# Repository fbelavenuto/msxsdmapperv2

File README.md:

# MSX SD Mapper V2

## WARNING: do not try to update the old SDMapper V1 (and its clones) with this new ROM using the old SDMUPD.COM utility, as the hardware is different, and it will brick your cartridge.

# Disclaimer

This documentation describes Open Hardware and is licensed under the CERN OHL v. 1.1.

You may redistribute and modify this documentation under the terms of the [CERN OHL v.1.1](http://ohwr.org/cernohl). This documentation is distributed WITHOUT ANY EXPRESS OR IMPLIED WARRANTY, INCLUDING OF MERCHANTABILITY, SATISFACTORY QUALITY AND FITNESS FOR A PARTICULAR PURPOSE.

Please see the CERN OHL v.1.1 for applicable conditions

# Project description

This project implements a cartridge-shaped interface to add a mass storage device using up to two SD (Secure Digital) and a 512K Mapper for MSX line computers.

[Nextor](http://www.konamiman.com/msx/msx-e.html#nextor) was used as operating system, being developed only the driver to have access to the two SD cards. Nextor is an open project.

Nextor is an evolution of MSX-DOS 2 natively supporting FAT16 partitions up to 4GB, and can have 4 partitions per SD card. 128KB of Mapper is required on the minimum to use Nextor with access to sub-directories, less than 128K mapper only allows the use of the MSXDOS1 kernel, limiting partitions with FAT12 and maximum 16MB per partition.

One of the switches enables or disables the Mapper in conjunction with a slot expander. The second key allows you to select between two driver options, useful for having a backup a stable version of the driver and use it to restore a new driver update failed.

A utility called "FBL-UPD.COM" was created to be able to update the flash by MSX itself.

To compile the FBL-UPD.COM driver and utility use the [Konaniman's Nestor80](https://github.com/Konamiman/Nestor80) and to compile the CPLD code use [Xilinx ISE Webpack](https://www.xilinx.com/support/download/index.html/content/xilinx/en/downloadNav/vivado-design-tools/archive-ise.html).

Technical details:
 - The CPLD code implements all the necessary logic, implementing an expander of standard slots, one SPI mode 0 port, standard ASCII16 MegaROM control used by Nextor and the 512K Mapper control.
 - When activating the mapper, the interface activates the slot expander, and with that the interface works only on non-expanded slots. However, if you disable the mapper, the slot expander is disabled, allowing you to use the device of mass storage in expanded slots. the mass storage device is in subslot 0 and the mapper device in subslot 1.
 - There is a window in $7B00~7EFF for SPI data transfer.
 - There is a configuration and status register at address $7FF0 and a small timer at address $7FF1. More details in the driver source.

# Acknowledge

Thanks to FRS for rewriting the driver, to Luciano Sturaro for board routing and the MSXBR-L community for their support and encouragement.

# Quickstart guide

After assembling the device, or buying a ready-made one, get an SD card, put it in the interface and start MSX.

When dropping into BASIC, type `CALL FDISK` to start formatting the SD card. The FAT16 file system used by Nextor supports a maximum of 4GB.

After partitioning and formatting, shut down MSX, remove the SD card and put it on your PC, copy the contents of the ./SD folder into the first partition of the SD card and put it back in MSX.

For more information on how to use Nextor, visit [User Manual](https://github.com/Konamiman/Nextor/blob/v2.1/docs/Nextor%202.1%20User%20Manual.md)

# 3D case

I found [this design](https://www.printables.com/en/model/496236-msx-cartridge-for-fblabs-sd-mapper-v2) made by community.

# Readme in portuguese

Este projeto implementa uma interface em forma de cartucho para adicionar um dispositivo de armazenamento em massa utilizando até dois cartões SD (Secure Digital) e uma Mapper de 512K para computadores da linha MSX.

Foi utilizado como sistema operacional o [Nextor](http://www.konamiman.com/msx/msx-e.html#nextor) sendo desenvolvido somente o driver para se ter acesso aos dois cartões SD. O Nextor é um projeto aberto.

O Nextor é uma evolução do MSX-DOS 2 tendo nativamente suporte a partições FAT16 de até 4GB, podendo ter 4 partições por cartão SD. É necessário 128KB de Mapper no mínimo para utilizar o Nextor com acesso à sub-diretórios, menos que 128K de mapper permite somente o uso do kernel do MSXDOS1 limitando em partições com FAT12 e máximo de 16MB por partição.

Uma das chaves habilita ou não a Mapper em conjunto com um expansor de slot. A segunda chave permite selecionar entre duas opções de driver, útil para se ter um backup de uma versão estável do driver e utilizá-lo para restaurar um driver novo com falha na atualização.

Foi criado um utilitário chamado "FBL-UPD.COM" para poder atualizar a flash pelo próprio MSX.

Para compilar o driver e o utilitário FBL-UPD.COM utilize o [Nestor80 do Konaniman](https://github.com/Konamiman/Nestor80) e para compilar o código do CPLD utilize o [Xilinx ISE Webpack](https://www.xilinx.com/support/download/index.html/content/xilinx/en/downloadNav/vivado-design-tools/archive-ise.html).

# Agradecimentos

Agradecimentos ao FRS pela re-escrita do driver, ao Luciano Sturaro pelo roteamento da placa e a comunidade MSXBR-L pelo apoio e incentivo.

# Detalhes técnicos:

 - O código do CPLD implementa toda a lógica necessária, implementando um expansor de slots padrão, uma porta SPI modo 0, o controle da MegaROM padrão ASCII16 utilizada pelo Nextor e o controle da Mapper de 512K.
 - Ao ativar a mapper, a interface ativa o expansor de slots, e com isso a interface funciona somente em slots não-expandidos. Porém, se desativar a mapper, o expansor de slots é desativado, permitindo utilizar o dispositivo de armazenamento em massa em slots expandidos. O dispositivo de armazenamento em massa fica no subslot 0 e a mapper no subslot 1.
 - Há uma janela em $7B00~7EFF para a transferência de dados SPI.
 - Existe um registro de configuração e status no endereço $7FF0 e um pequeno timer no endereço $7FF1. Mais detalhes no source do driver.

# Início rápido

Depois de montar o dispositivo, ou comprar um pronto, adquira um cartão SD, coloque na interface e inicie o MSX.

Ao cair no BASIC, digite `CALL FDISK` para iniciar a formatação do cartão SD. O sistema de arquivos FAT16 utilizado pelo Nextor suporta no máximo 4GB.

Após o particionamento e formatação, desligue o MSX, retire o cartão SD e coloque no seu PC, copie o conteúdo da pasta ./SD para dentro da primeira partição do cartão SD e recoloque no MSX.

Maiores informações de como usar o Nextor acesse o [Manual do usuário](https://github.com/Konamiman/Nextor/blob/v2.1/docs/Nextor%202.1%20User%20Manual.md)

# Case 3D

Eu achei [este desenho](https://www.printables.com/en/model/496236-msx-cartridge-for-fblabs-sd-mapper-v2) feito pela comunidade.

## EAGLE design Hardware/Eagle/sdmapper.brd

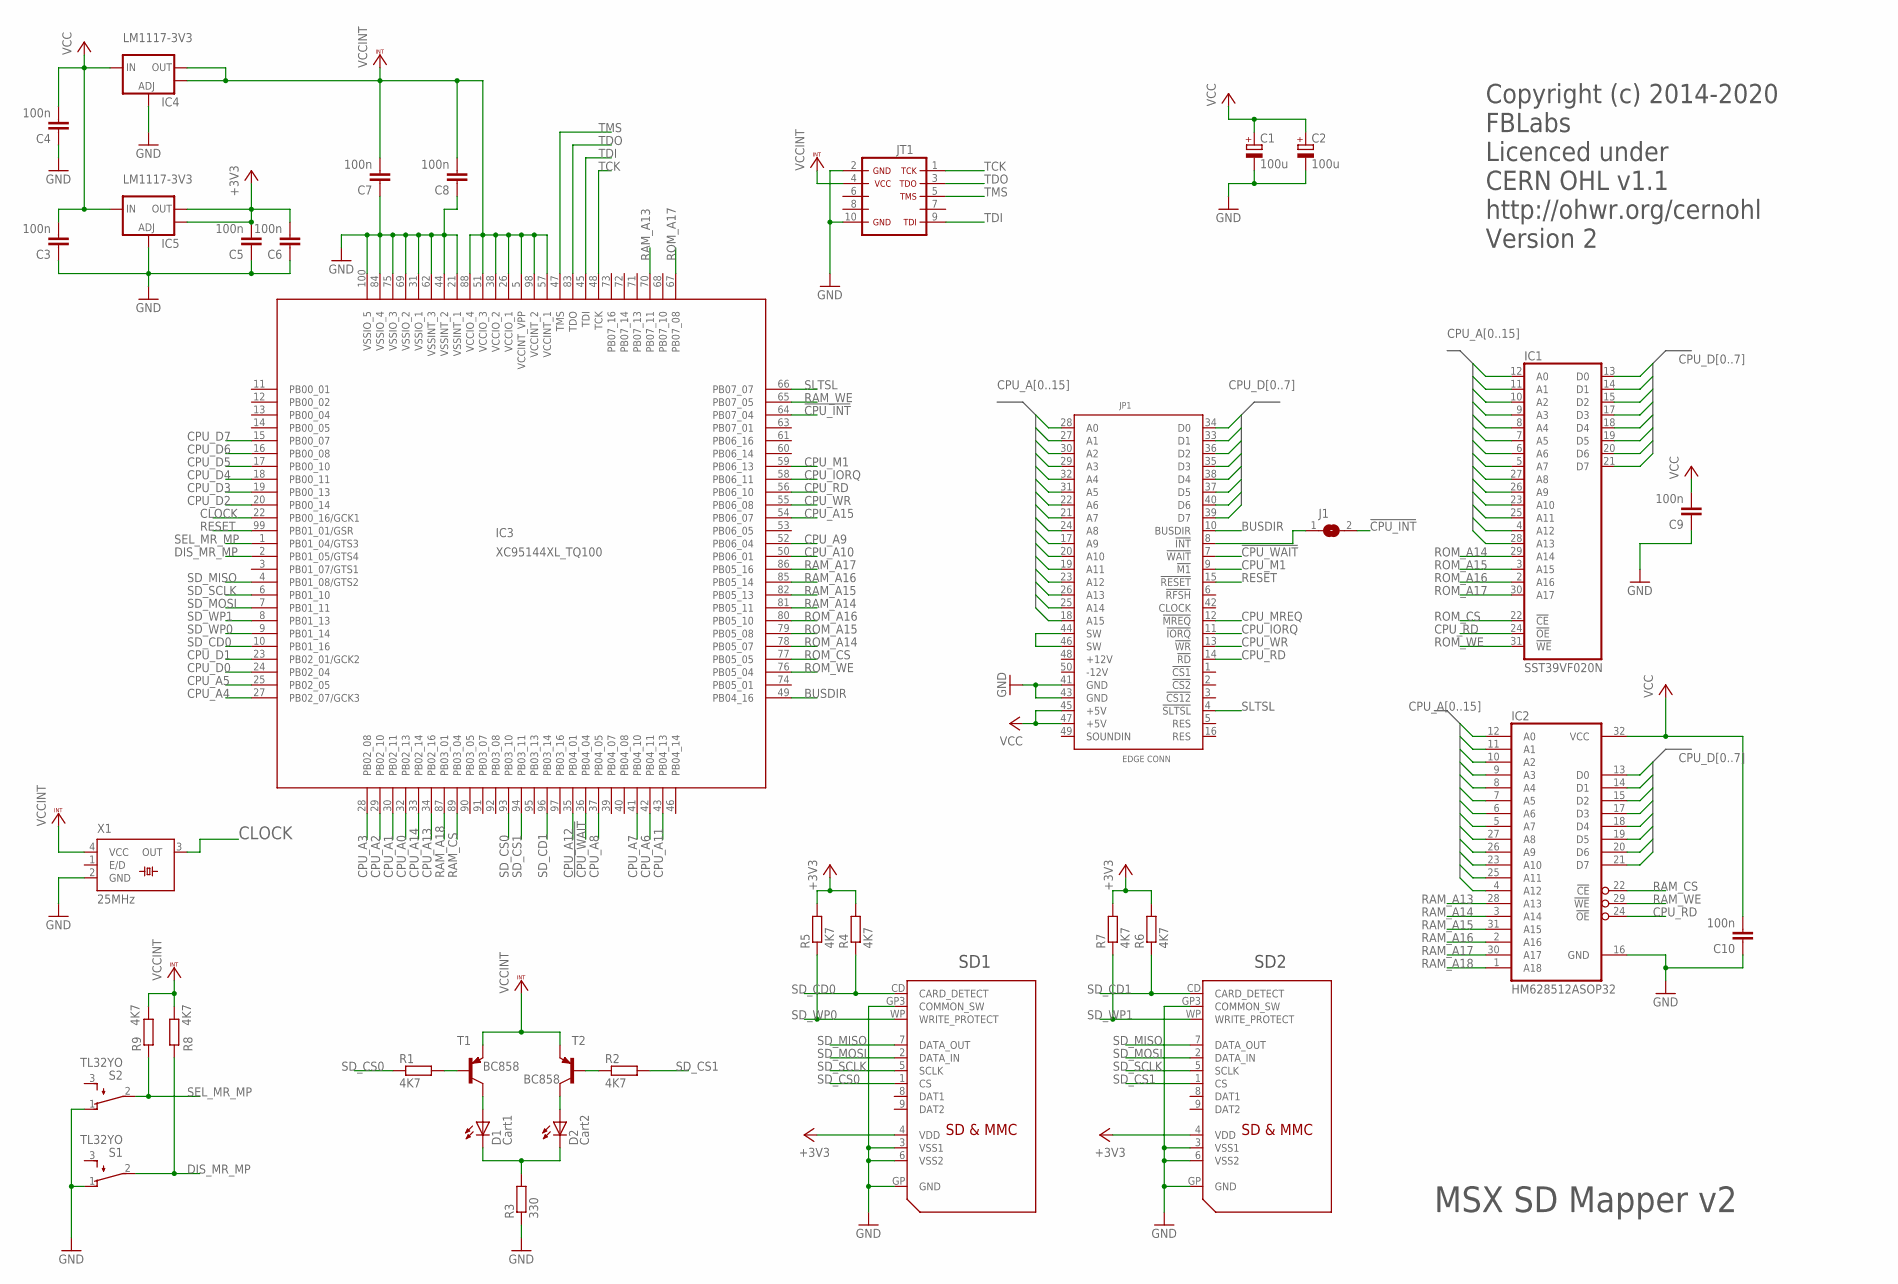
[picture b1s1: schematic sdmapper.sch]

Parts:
C1: 100u; E3,5-6
C2: 100u; PANASONIC_C
C3, C4, C5, C6, C7, C8, C9, C10: 100n; C0805
D1: Cart1; LED3MM
D2: Cart2; LED3MM
IC1: SST39VF020N; PLCC32R
IC2: HM628512ASOP32; SOP32
IC3: XC95144XL_TQ100; XC-TQ100
IC4, IC5: LM1117-3V3; SOT223
J1: SJ4; SJ20
JP1: MSXCART1; MSXCART
JT1: JTAG1B; SMD5X2
R1, R2, R4, R5, R6, R7, R8, R9: 4K7; R0805
R3: 330; R0805
S1, S2: TL32YO; TL3XYO
SD1, SD2: SDMMC06132; 06132
T1, T2: BC858; SOT23-BEC
X1: 25MHz; SM77H

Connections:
!CPU_INT: IC3.64 (PB07_04), J1.2
!CPU_WAIT: IC3.36 (PB04_04), JP1.7 (!WAIT)
+3V3: C5.2, C6.2, IC5.2 (OUT), IC5.4 (OUT), R4.2, R5.2, R6.2, R7.2, SD1.4 (VDD), SD2.4 (VDD)
BUSDIR: IC3.49 (PB04_16), JP1.10 (BUSDIR)
CLOCK: IC3.22 (PB00_16/GCK1), X1.3 (OUT)
CPU_A0: IC1.12 (A0), IC2.12 (A0), IC3.32 (PB02_13), JP1.28 (A0)
CPU_A1: IC1.11 (A1), IC2.11 (A1), IC3.30 (PB02_11), JP1.27 (A1)
CPU_A2: IC1.10 (A2), IC2.10 (A2), IC3.29 (PB02_10), JP1.30 (A2)
CPU_A3: IC1.9 (A3), IC2.9 (A3), IC3.28 (PB02_08), JP1.29 (A3)
CPU_A4: IC1.8 (A4), IC2.8 (A4), IC3.27 (PB02_07/GCK3), JP1.32 (A4)
CPU_A5: IC1.7 (A5), IC2.7 (A5), IC3.25 (PB02_05), JP1.31 (A5)
CPU_A6: IC1.6 (A6), IC2.6 (A6), IC3.42 (PB04_11), JP1.22 (A6)
CPU_A7: IC1.5 (A7), IC2.5 (A7), IC3.41 (PB04_10), JP1.21 (A7)
CPU_A8: IC1.27 (A8), IC2.27 (A8), IC3.37 (PB04_05), JP1.24 (A8)
CPU_A9: IC1.26 (A9), IC2.26 (A9), IC3.52 (PB06_04), JP1.17 (A9)
CPU_A10: IC1.23 (A10), IC2.23 (A10), IC3.50 (PB06_01), JP1.20 (A10)
CPU_A11: IC1.25 (A11), IC2.25 (A11), IC3.43 (PB04_13), JP1.19 (A11)
CPU_A12: IC1.4 (A12), IC2.4 (A12), IC3.35 (PB04_01), JP1.23 (A12)
CPU_A13: IC1.28 (A13), IC3.34 (PB02_16), JP1.26 (A13)
CPU_A14: IC3.33 (PB02_14), JP1.25 (A14)
CPU_A15: IC3.54 (PB06_07), JP1.18 (A15)
CPU_D0: IC1.13 (D0), IC2.13 (D0), IC3.24 (PB02_04), JP1.34 (D0)
CPU_D1: IC1.14 (D1), IC2.14 (D1), IC3.23 (PB02_01/GCK2), JP1.33 (D1)
CPU_D2: IC1.15 (D2), IC2.15 (D2), IC3.20 (PB00_14), JP1.36 (D2)
CPU_D3: IC1.17 (D3), IC2.17 (D3), IC3.19 (PB00_13), JP1.35 (D3)
CPU_D4: IC1.18 (D4), IC2.18 (D4), IC3.18 (PB00_11), JP1.38 (D4)
CPU_D5: IC1.19 (D5), IC2.19 (D5), IC3.17 (PB00_10), JP1.37 (D5)
CPU_D6: IC1.20 (D6), IC2.20 (D6), IC3.16 (PB00_08), JP1.40 (D6)
CPU_D7: IC1.21 (D7), IC2.21 (D7), IC3.15 (PB00_07), JP1.39 (D7)
CPU_IORQ: IC3.58 (PB06_11), JP1.11 (!IORQ)
CPU_M1: IC3.59 (PB06_13), JP1.9 (!M1)
CPU_MREQ: JP1.12 (!MREQ)
CPU_RD: IC1.24 (!OE), IC2.24 (!OE), IC3.56 (PB06_10), JP1.14 (!RD)
CPU_WR: IC3.55 (PB06_08), JP1.13 (!WR)
DIS_MR_MP: IC3.2 (PB01_05/GTS4), R8.1, S1.2
GND: C1.-, C2.-, C3.1, C4.1, C5.1, C6.1, C7.1, C8.1, C9.1, C10.1, IC1.16 (GND), IC2.16 (GND), IC3.21 (VSSINT_1), IC3.31 (VSSIO_1), IC3.44 (VSSINT_2), IC3.62 (VSSINT_3), IC3.69 (VSSIO_2), IC3.75 (VSSIO_3), IC3.84 (VSSIO_4), IC3.100 (VSSIO_5), IC4.1 (ADJ), IC5.1 (ADJ), JP1.41 (GND), JP1.43 (GND), JT1.2, JT1.10, R3.1, S1.1 (O), S2.1 (O), SD1.3 (VSS1), SD1.6 (VSS2), SD1.GP (GND), SD1.GP3 (COMMON_SW), SD2.3 (VSS1), SD2.6 (VSS2), SD2.GP (GND), SD2.GP3 (COMMON_SW), X1.2 (GND)
unnamed: JP1.44 (SW), JP1.46 (SW)
unnamed: J1.1, JP1.8 (!INT)
unnamed: R1.2, T1.B
unnamed: R2.1, T2.B
unnamed: D1.K (C), D2.K (C), R3.2
unnamed: D1.A, T1.C
unnamed: D2.A, T2.C
RAM_A13: IC2.28 (A13), IC3.70 (PB07_11)
RAM_A14: IC2.3 (A14), IC3.81 (PB05_11)
RAM_A15: IC2.31 (A15), IC3.82 (PB05_13)
RAM_A16: IC2.2 (A16), IC3.85 (PB05_14)
RAM_A17: IC2.30 (A17), IC3.86 (PB05_16)
RAM_A18: IC2.1 (A18), IC3.87 (PB03_01)
RAM_CS: IC2.22 (!CE), IC3.89 (PB03_04)
RAM_WE: IC2.29 (!WE), IC3.65 (PB07_05)
RESET: IC3.99 (PB01_01/GSR), JP1.15 (!RESET)
ROM_A14: IC1.29 (A14), IC3.78 (PB05_07)
ROM_A15: IC1.3 (A15), IC3.79 (PB05_08)
ROM_A16: IC1.2 (A16), IC3.80 (PB05_10)
ROM_A17: IC1.30 (A17), IC3.67 (PB07_08)
ROM_CS: IC1.22 (!CE), IC3.77 (PB05_05)
ROM_WE: IC1.31 (!WE), IC3.76 (PB05_04)
SD_CD0: IC3.10 (PB01_16), R4.1, SD1.CD (CARD_DETECT)
SD_CD1: IC3.96 (PB03_14), R6.1, SD2.CD (CARD_DETECT)
SD_CS0: IC3.93 (PB03_10), R1.1, SD1.1 (CS)
SD_CS1: IC3.94 (PB03_11), R2.2, SD2.1 (CS)
SD_MISO: IC3.4 (PB01_08/GTS2), SD1.7 (DATA_OUT), SD2.7 (DATA_OUT)
SD_MOSI: IC3.7 (PB01_11), SD1.2 (DATA_IN), SD2.2 (DATA_IN)
SD_SCLK: IC3.6 (PB01_10), SD1.5 (SCLK), SD2.5 (SCLK)
SD_WP0: IC3.9 (PB01_14), R5.1, SD1.WP (WRITE_PROTECT)
SD_WP1: IC3.8 (PB01_13), R7.1, SD2.WP (WRITE_PROTECT)
SEL_MR_MP: IC3.1 (PB01_04/GTS3), R9.1, S2.2
SLTSL: IC3.66 (PB07_07), JP1.4 (!SLTSL)
TCK: IC3.48 (TCK), JT1.1
TDI: IC3.45 (TDI), JT1.9
TDO: IC3.83 (TDO), JT1.3
TMS: IC3.47 (TMS), JT1.5
VCC: C1.+, C2.+, C3.2, C4.2, C9.2, C10.2, IC1.32 (VCC), IC2.32 (VCC), IC4.3 (IN), IC5.3 (IN), JP1.45 (+5V), JP1.47 (+5V)
VCCINT: C7.2, C8.2, IC3.5 (VCCINT_VPP), IC3.26 (VCCIO_1), IC3.38 (VCCIO_2), IC3.51 (VCCIO_3), IC3.57 (VCCINT_1), IC3.88 (VCCIO_4), IC3.98 (VCCINT_2), IC4.2 (OUT), IC4.4 (OUT), JT1.4, R8.2, R9.2, T1.E, T2.E, X1.4 (VCC)

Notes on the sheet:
MSX SD Mapper v2
Copyright (c) 2014-2020 FBLabs Licenced under CERN OHL v1.1 http://ohwr.org/cernohl Version 2
SD1
SD2

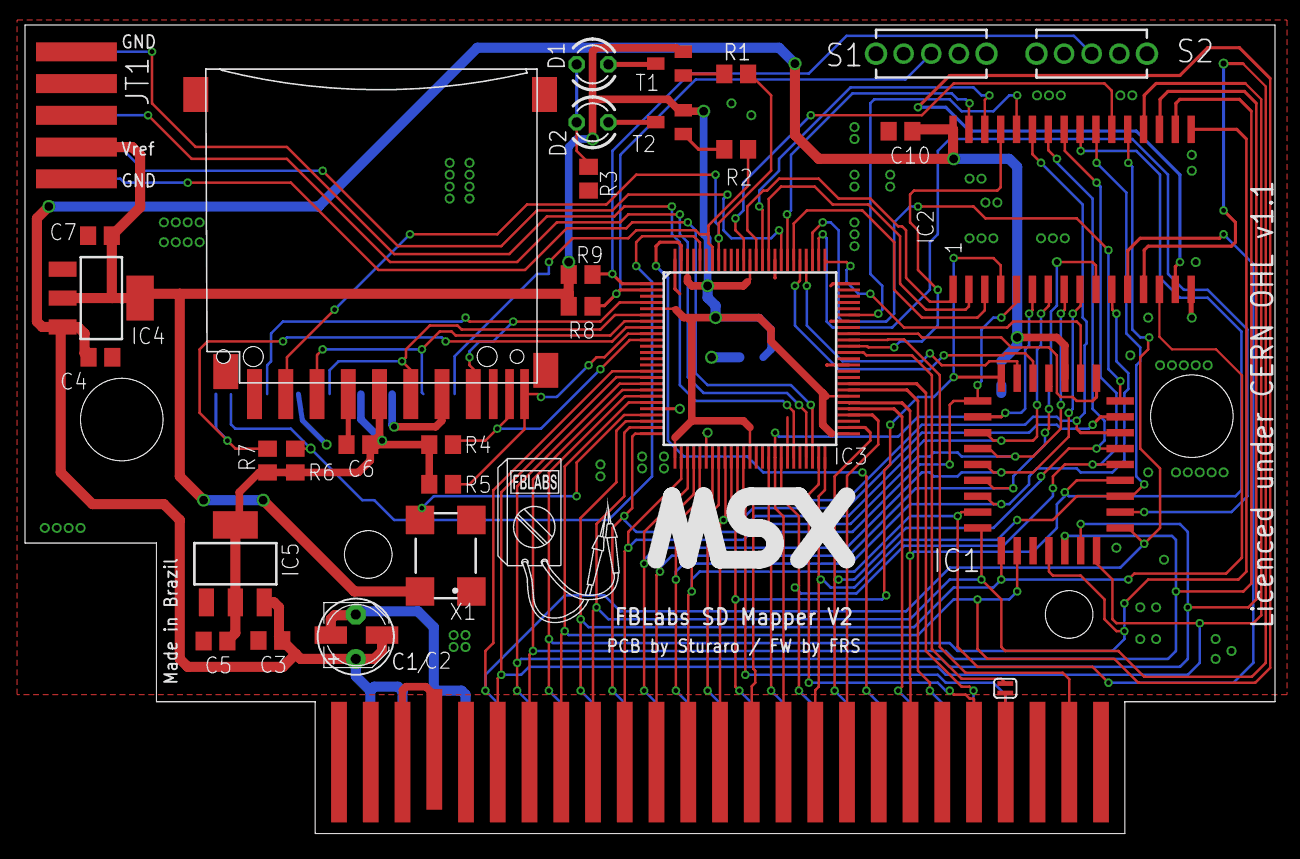
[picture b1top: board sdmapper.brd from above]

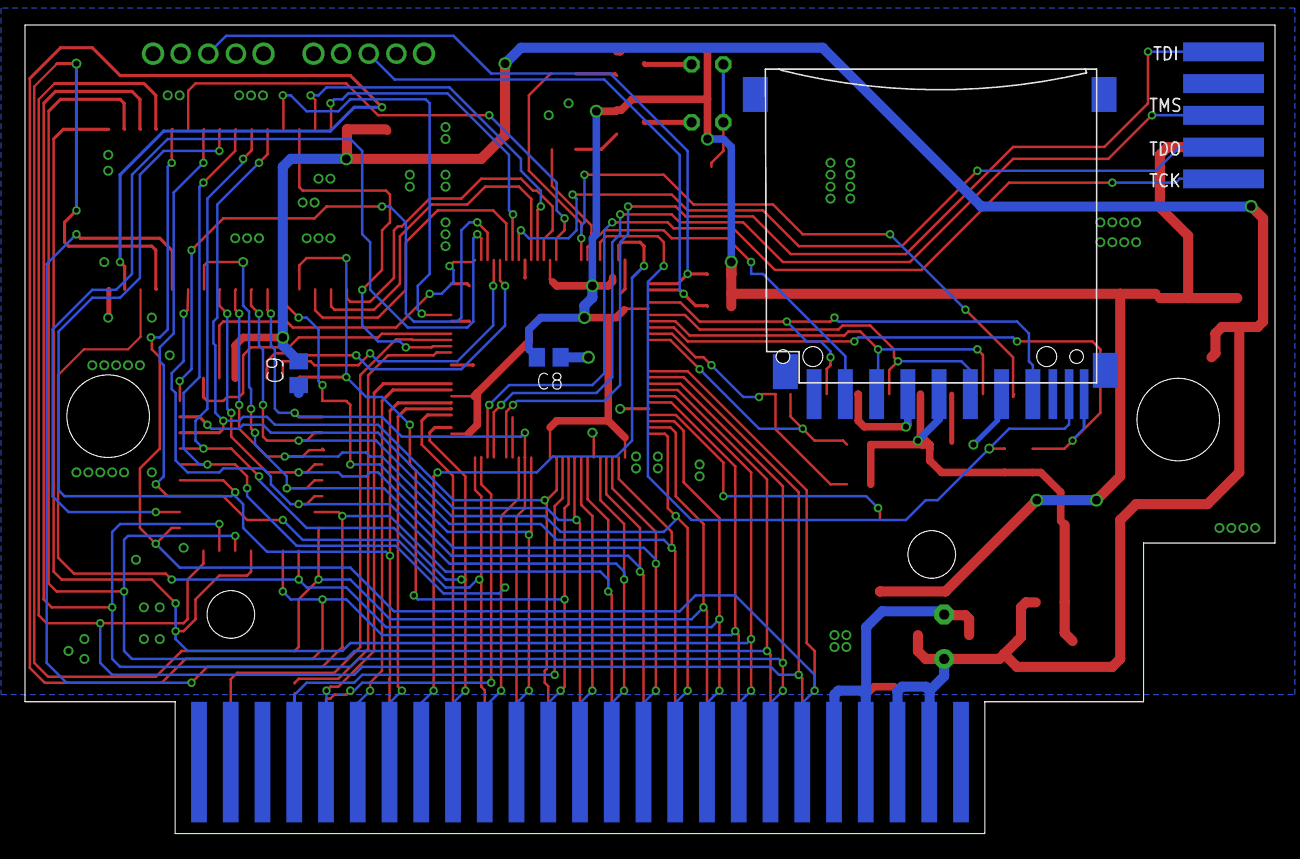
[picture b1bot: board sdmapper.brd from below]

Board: 2 copper layers, 100.0 x 64.7 mm, 38 parts (3 on the bottom side), 74 nets.

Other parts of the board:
U$1: LOGO_FABIO_SILK_400MIL
U$3: MSX_SILK

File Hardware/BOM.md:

# Bill of Materials

| Part | Value | Package | Description |
|:----:|-------|---------|-------------|
| R1 | 4K7 | 0805 | Resistor |
| R2 | 4K7 | 0805 | Resistor |
| R3 | 330 | 0805 | Resistor |
| R4 | 4K7 | 0805 | Resistor |
| R5 | 4K7 | 0805 | Resistor |
| R6 | 4K7 | 0805 | Resistor |
| R7 | 4K7 | 0805 | Resistor |
| R8 | 4K7 | 0805 | Resistor |
| R9 | 4K7 | 0805 | Resistor |
| C1 | 100u | E3,5-6 | Polarized capacitor (see note #1) |
| C2 | 100u | SMD EUC | Polarized capacitor (see note #1) |
| C3 | 100n | SMD 0805 | Capacitor |
| C4 | 100n | SMD 0805 | Capacitor |
| C5 | 100n | SMD 0805 | Capacitor |
| C6 | 100n | SMD 0805 | Capacitor |
| C7 | 100n | SMD 0805 | Capacitor |
| C8 | 100n | SMD 0805 | Capacitor |
| C9 | 100n | SMD 0805 | Capacitor |
| C10 | 100n | SMD 0805 | Capacitor |
| D1 | Cart1 | 3mm | LED 3mm any color |
| D2 | Cart2 | 3mm | LED 3mm any color |
| T1 | BC858 | SOT23-BEC | PNP Transistor |
| T2 | BC858 | SOT23-BEC | PNP Transistor |
| X1 | 25MHz | SM77H | 3.3V CMOS Clock Oscillator |
| IC1 | *see note #2 | PLCC32 | 2 Mbit x8 Multi-Purpose Flash |
| IC2 | 628512 | SOP32 | 4M SRAM 512kword x 8bit |
| IC3 | XC95144XL |TQ100 | XC95144XL-TQ100 |
| IC4 | LM1117-3V3 | SOT223 | Voltage Regulator LM1117
| IC5 | LM1117-3V3 | SOT223 | Voltage Regulator LM1117
| S1 | TL32YO | TL3XYO | TINY SWITCH ON - MOM |
| S2 | TL32YO | TL3XYO | TINY SWITCH ON - MOM |
| SD1 | SDMMC06132 | 06132 | SD MMC Card holder |
| SD2 | SDMMC06132 | 06132 | SD MMC Card holder |

### Notes:
 - 1 - Use C1 or C2
 - 2 - Possible models: SST39SF020, AT49F002, AT49F002T, SST39SF020, W49F002UN or W49F002B

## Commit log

2020-04-15 Primeiro envio
2021-01-15 Liberação para o público
2021-03-02 Added schematic.pdf
2022-02-11 Added sdmapper.jed
2022-10-27 Documentation
2022-12-02 Update driver.asm
    Added a comment about the ASCII16 ROM mapper and the page where the interface register set is enabled.
2023-12-05 Converting to compile with N80
2023-12-06 Fixing case of filenames
2023-12-11 Organizing Files, Compiling bitstream with docker
2023-12-11 Renaming SD files to uppercase
2023-12-12 Updating MAPDRV.COM, adding EPTCFT.COM
2023-12-17 Adapting updater to new msxclib (port to new sdcc call convention)
2023-12-17 build: avoid unnecessary export
2023-12-17 fix: replace backslashes
2023-12-17 build: keep bourne shell compatibility
2023-12-17 fix: filename case
2024-02-15 Adding 3D case link
2024-05-03 Adding missing eagle files
2024-06-30 docs: add front assembly
2024-07-01 Alterando PCB e gerbers para retirar o logo PalMal
2024-07-04 Corrigindo Gerbers

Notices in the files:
parts and their libraries:
SparkFun-PowerIC: Licensing: CC v3.0 Share-Alike You are welcome to use this library for commercial purposes.
